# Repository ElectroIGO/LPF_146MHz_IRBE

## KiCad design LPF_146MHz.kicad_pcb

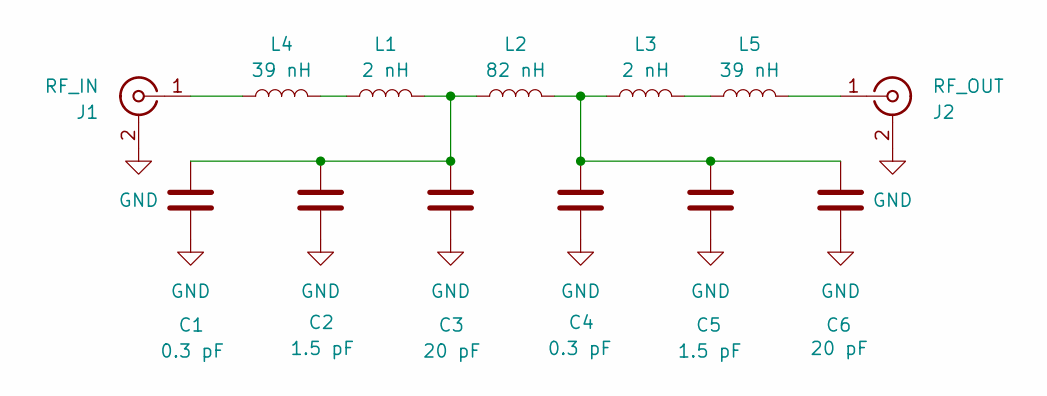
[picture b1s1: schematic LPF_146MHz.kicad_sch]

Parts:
C1, C4: 0.3 pF; C_0603_1608Metric
C2, C5: 1.5 pF; C_0603_1608Metric
C3, C6: 20 pF; C_0603_1608Metric
J1: RF_IN; SMA_CHINA
J2: RF_OUT; SMA_CHINA
L1, L3: 2 nH; L_0603_1608Metric
L2: 82 nH; L_0603_1608Metric
L4, L5: 39 nH; L_0603_1608Metric

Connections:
GND: C1.2, C2.2, C3.2, C4.2, C5.2, C6.2, J1.2 (Ext), J2.2 (Ext)
unnamed: C1.1, C2.1, C3.1, L1.2, L2.1
unnamed: C4.1, C5.1, C6.1, L2.2, L3.1
unnamed: J1.1 (In), L4.1
unnamed: J2.1 (In), L5.2
unnamed: L1.1, L4.2
unnamed: L3.2, L5.1

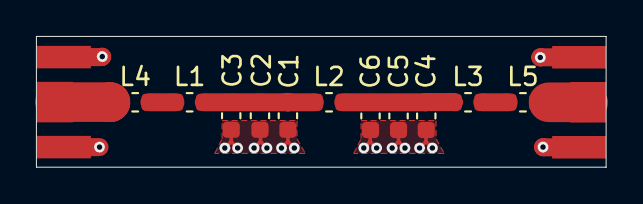
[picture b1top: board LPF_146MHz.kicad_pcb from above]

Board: 2 copper layers, 31.6 x 7.3 mm, 13 parts (0 on the bottom side), 7 nets.

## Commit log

2024-09-11 Finished LPF for IRBE radio amateurs
